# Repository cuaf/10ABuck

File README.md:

10 Amp Buck
===========

Based on TI SimpleSwitcher.

Designed as a quick way to get plenty of power for our servos or avionics. More reliable under load than the 3A BECs you can buy off of the shelf
TI offer free sampling of these parts for academic or student projects. 

Now also features an optional 3v3 LDO. 

Need to look at the heat dissipation, it's a switcher, but the board area may need to be increased to dissipate heat if we're using these at near full capacity. 
With 2 square inches of copper for heat dissipation we hit 21degs/W rise. 
This gives us about 3W of dissipation to play with before things get too hot, or 6A switching down. This isn't much of an improvement over the current power supply board on the quad from last year, but it is in a far smaller package (1.85x1.5 inches). If we increased the board area, we'd be fine. The package is also compatible with D3-pak smd heat sinks.

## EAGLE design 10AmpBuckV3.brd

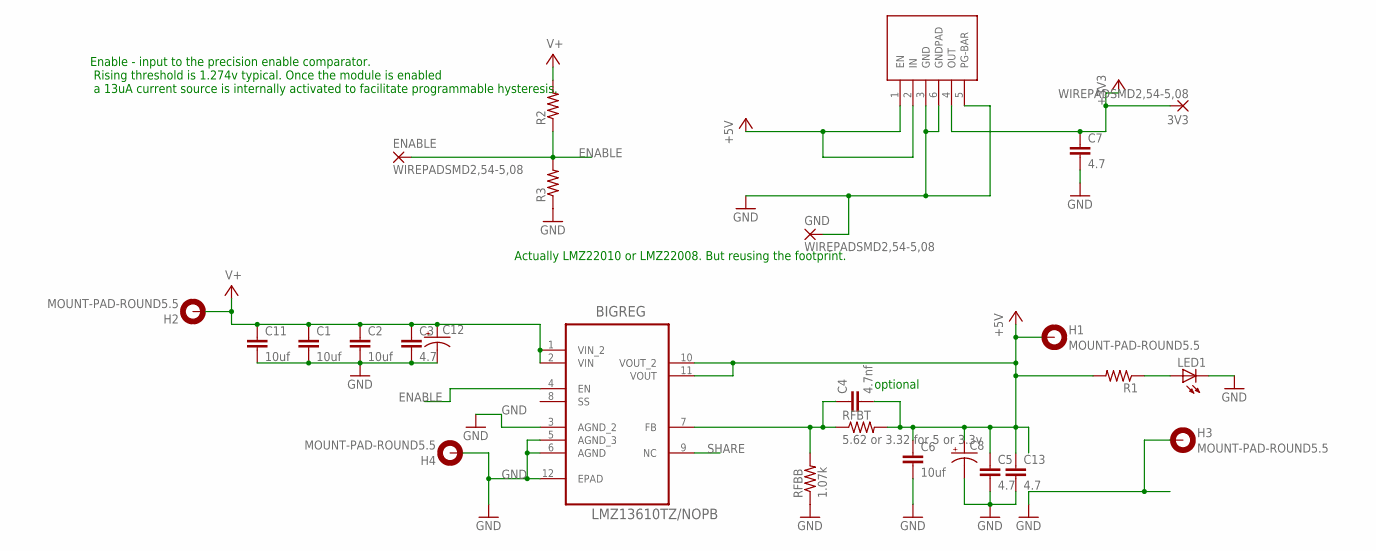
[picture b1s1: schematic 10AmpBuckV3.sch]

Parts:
3V3: WIREPADSMD2,54-5,08; SMD2,54-5,08
BIGREG: LMZ13610TZ/NOPB; TI_TO-PMOD-11
C1, C2, C6, C11: 10uf; 1206
C3, C5, C7, C13: 4.7; 1206
C4: 4.7nf; 0603-CAP
C8, C12: CAP_POLPTH1; CPOL-RADIAL-100UF-25V
ENABLE: WIREPADSMD2,54-5,08; SMD2,54-5,08
GND: WIREPADSMD2,54-5,08; SMD2,54-5,08
H1, H2, H3, H4: MOUNT-PAD-ROUND5.5; 5,5-PAD
LED1: LED1206; LED-1206
R1, R2, R3: RESISTOR0603-RES; 0603-RES
RFBB: 1.07k; 0603-RES
RFBT: 5.62 or 3.32 for 5 or 3.3v; 0603-RES
U$1: TPS75533; TO263-5

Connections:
+3V3: 3V3.1, C7.1, U$1.4 (OUT)
+5V: BIGREG.10 (VOUT_2), BIGREG.11 (VOUT), C4.2, C5.1, C6.1, C8.1 (+), C13.1, H1.B5,5, R1.2, RFBT.2, U$1.1 (EN), U$1.2 (IN)
ENABLE: BIGREG.4 (EN), ENABLE.1, R2.1, R3.2
GND: BIGREG.3 (AGND_2), BIGREG.5 (AGND_3), BIGREG.6 (AGND), BIGREG.12 (EPAD), C1.2, C2.2, C3.2, C5.2, C6.2, C7.2, C8.2 (-), C11.2, C12.2 (-), C13.2, GND.1, H3.B5,5, H4.B5,5, LED1.C, R3.1, RFBB.1, U$1.3 (GND), U$1.5 (PG-BAR), U$1.6 (GNDPAD)
unnamed: BIGREG.7 (FB), C4.1, RFBB.2, RFBT.1
unnamed: LED1.A, R1.1
SHARE: BIGREG.9 (NC)
V+: BIGREG.1 (VIN_2), BIGREG.2 (VIN), C1.1, C2.1, C3.1, C11.1, C12.1 (+), H2.B5,5, R2.2

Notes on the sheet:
Actually LMZ22010 or LMZ22008. But reusing the footprint.
optional
Enable - input to the precision enable comparator. Rising threshold is 1.274v typical. Once the module is enabled a 13uA current source is internally activated to facilitate programmable hysteresis.

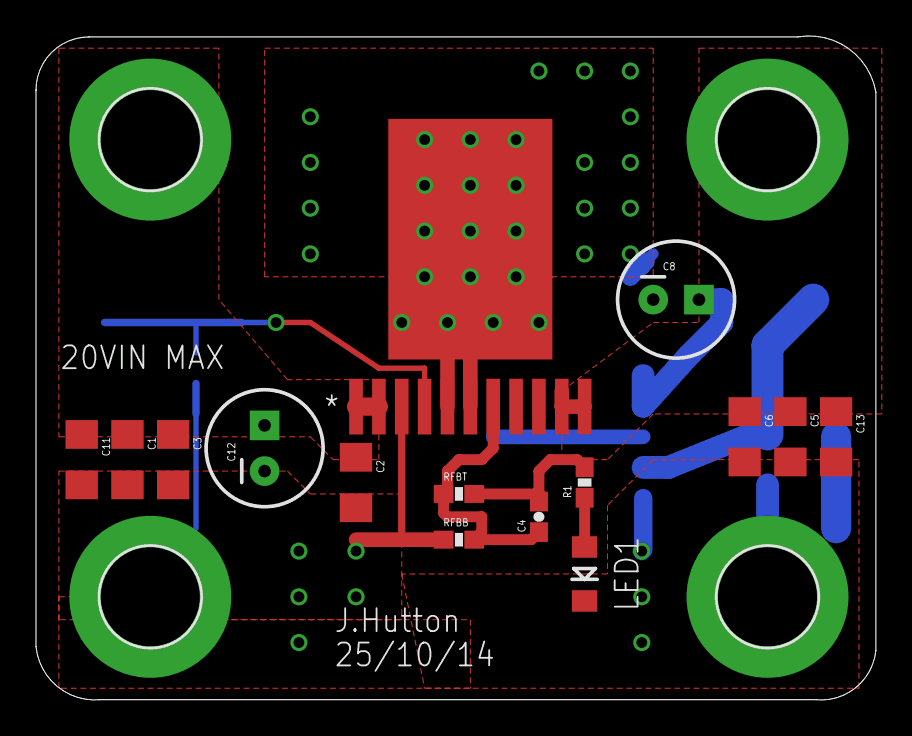
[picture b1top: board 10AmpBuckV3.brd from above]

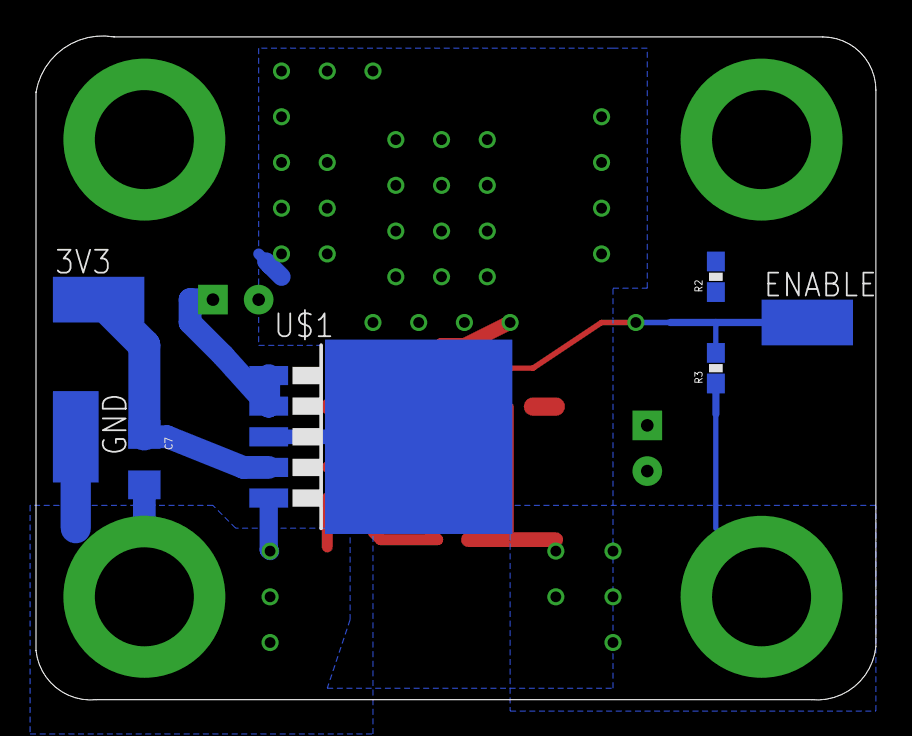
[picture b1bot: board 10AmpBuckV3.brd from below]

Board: 2 copper layers, 46.7 x 36.9 mm, 26 parts (7 on the bottom side), 7 nets.

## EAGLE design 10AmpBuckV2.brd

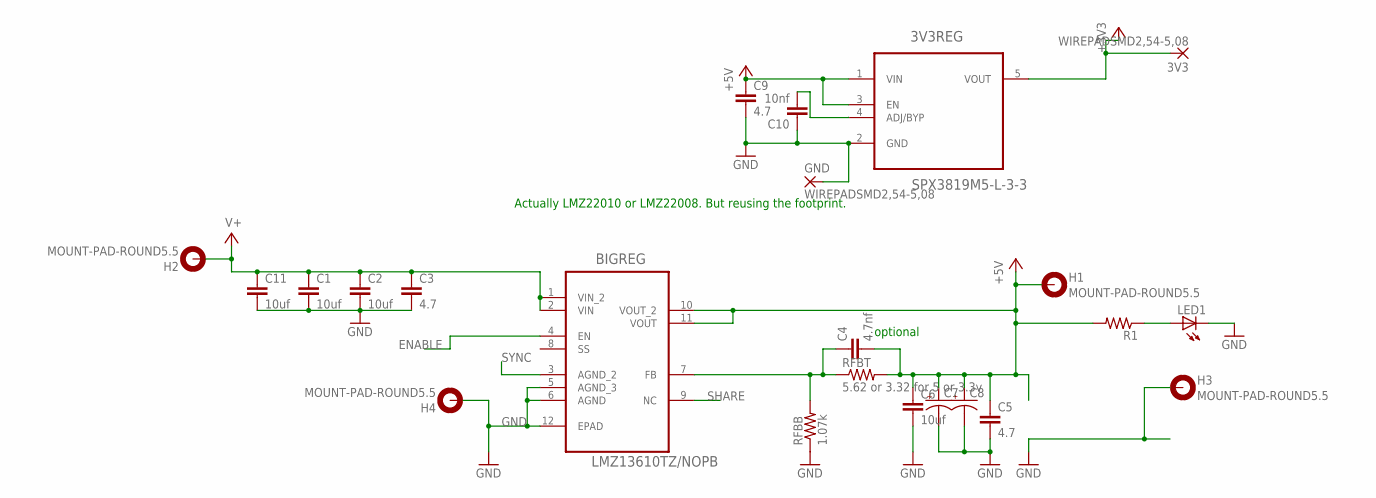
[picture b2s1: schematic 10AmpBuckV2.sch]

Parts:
3V3: WIREPADSMD2,54-5,08; SMD2,54-5,08
3V3REG: SPX3819M5-L-3-3; SOT95P280X145-5N
BIGREG: LMZ13610TZ/NOPB; TI_TO-PMOD-11
C1, C2, C6, C11: 10uf; 1206
C3, C5, C9: 4.7; 1206
C4: 4.7nf; 0603-CAP
C7, C8: CAP_POLPTH2; CPOL-RADIAL-10UF-25V
C10: 10nf; 0603-CAP
GND: WIREPADSMD2,54-5,08; SMD2,54-5,08
H1, H2, H3, H4: MOUNT-PAD-ROUND5.5; 5,5-PAD
LED1: LED1206; LED-1206
R1: RESISTOR0603-RES; 0603-RES
RFBB: 1.07k; 0603-RES
RFBT: 5.62 or 3.32 for 5 or 3.3v; 0603-RES

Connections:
+3V3: 3V3.1, 3V3REG.5 (VOUT)
+5V: 3V3REG.1 (VIN), 3V3REG.3 (EN), BIGREG.10 (VOUT_2), BIGREG.11 (VOUT), C4.2, C5.1, C6.1, C7.1 (+), C8.1 (+), C9.1, H1.B5,5, R1.2, RFBT.2
ENABLE: BIGREG.4 (EN)
GND: 3V3REG.2 (GND), BIGREG.5 (AGND_3), BIGREG.6 (AGND), BIGREG.12 (EPAD), C1.2, C2.2, C3.2, C5.2, C6.2, C7.2 (-), C8.2 (-), C9.2, C10.1, C11.2, GND.1, H3.B5,5, H4.B5,5, LED1.C, RFBB.1
unnamed: 3V3REG.4 (ADJ/BYP), C10.2
unnamed: BIGREG.7 (FB), C4.1, RFBB.2, RFBT.1
unnamed: LED1.A, R1.1
SHARE: BIGREG.9 (NC)
SYNC: BIGREG.3 (AGND_2)
V+: BIGREG.1 (VIN_2), BIGREG.2 (VIN), C1.1, C2.1, C3.1, C11.1, H2.B5,5

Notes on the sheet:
Actually LMZ22010 or LMZ22008. But reusing the footprint.
optional

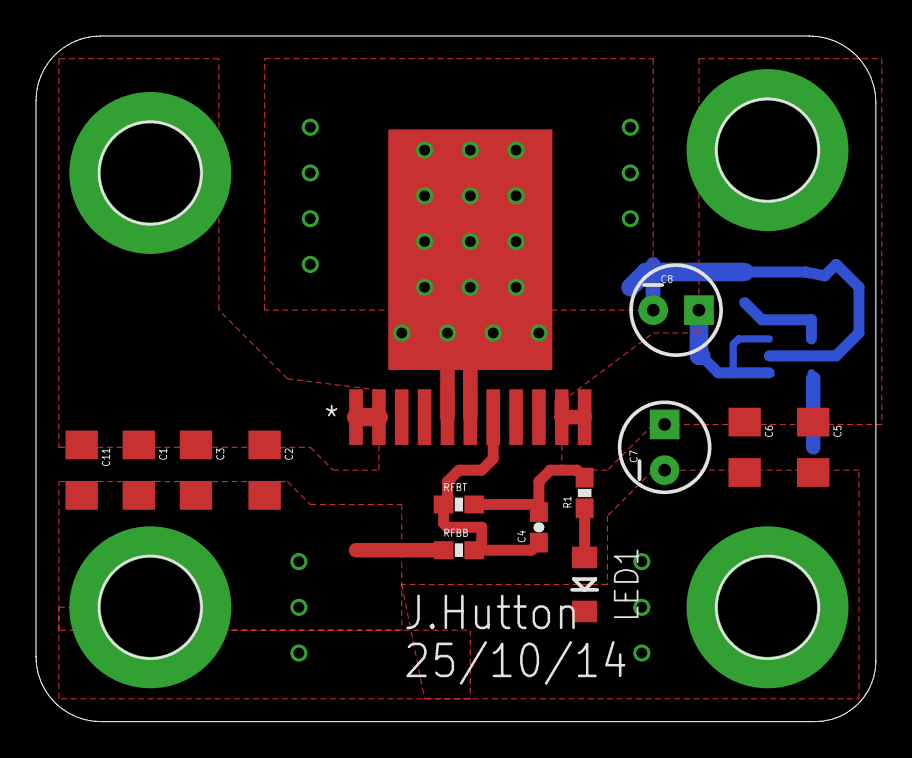
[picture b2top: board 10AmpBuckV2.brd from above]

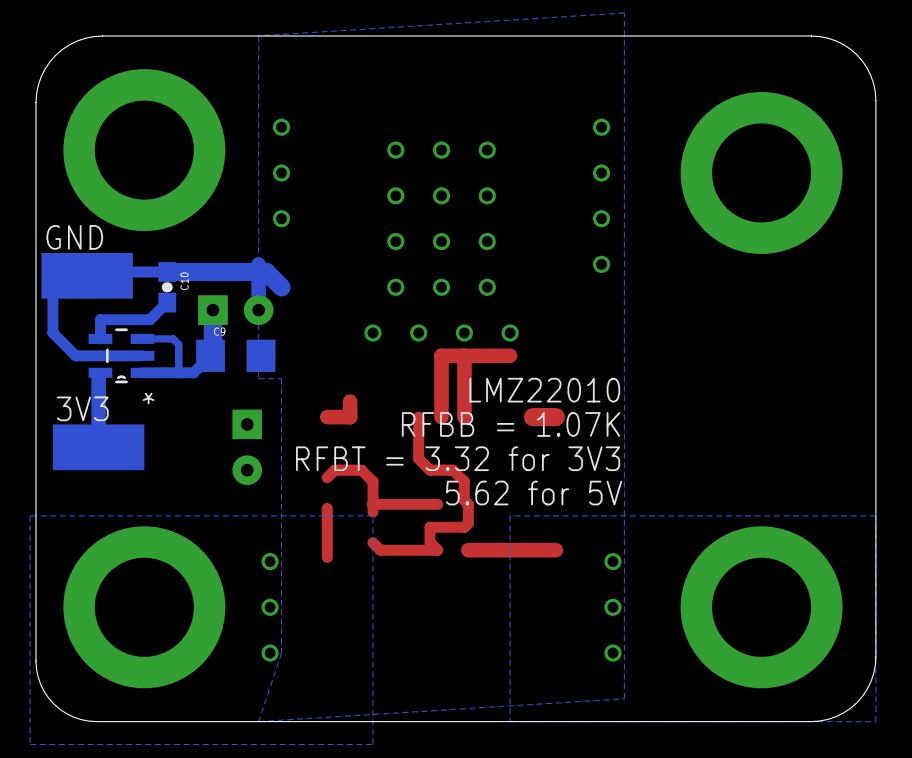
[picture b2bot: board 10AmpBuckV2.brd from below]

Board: 2 copper layers, 46.7 x 38.1 mm, 23 parts (5 on the bottom side), 7 nets.

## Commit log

2014-11-11 readme
2014-11-16 add enable, optiona 3v3 regulator
2014-11-16 refining
2014-11-16 removing the attic folder

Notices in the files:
parts and their libraries:
SparkFun-Passives: Licensing: CC v3.0 Share-Alike You are welcome to use this library for commercial purposes.
